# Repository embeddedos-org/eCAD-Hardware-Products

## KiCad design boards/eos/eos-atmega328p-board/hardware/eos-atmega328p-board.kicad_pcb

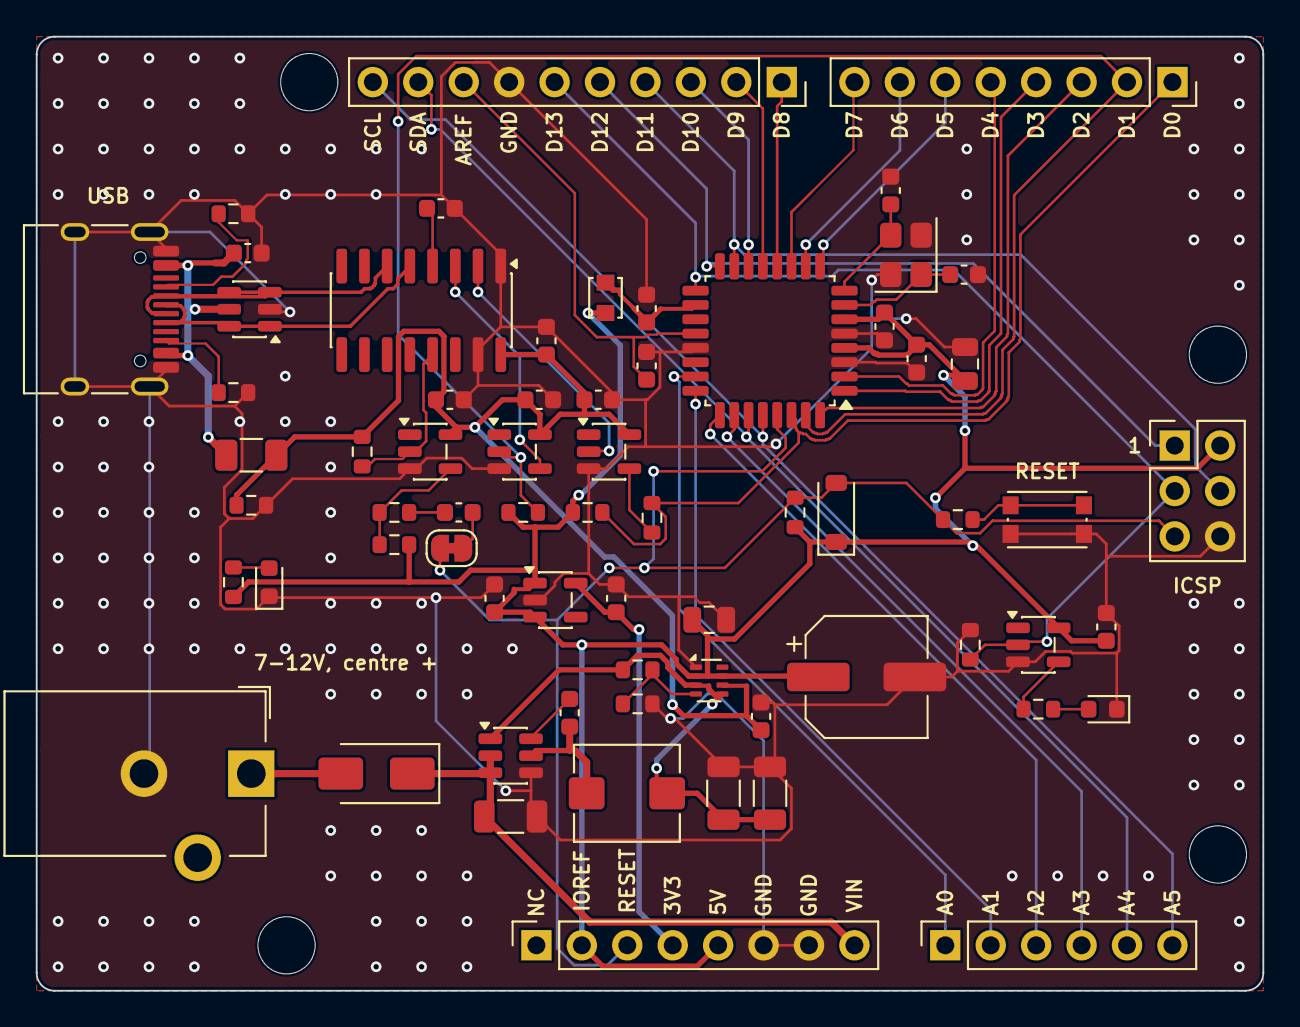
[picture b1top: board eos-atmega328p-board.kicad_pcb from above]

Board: 2 copper layers, 68.6 x 53.3 mm, 71 parts (1 on the bottom side), 52 nets.

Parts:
C1: 10u; C_1206_3216Metric
C2, C9, C10, C11, C12, C13, C15, C16, C19, C21, C22, C23, C24: 100n; C_0603_1608Metric
C3, C4: 22u; C_1206_3216Metric
C5, C7, C8: 1u; C_0603_1608Metric
C6: 100u; CP_Elec_6.3x5.8
C14, C20: 10u; C_0805_2012Metric
C17, C18: 18p; C_0603_1608Metric
D1: B240A; D_SMA
D2: PWR; LED_0603_1608Metric
D3: 1N4148W; D_SOD-123
D4: L; LED_0603_1608Metric
F1: 500mA; Fuse_1206_3216Metric
H1, H2, H3, H4: M3; MountingHole_3.2mm_M3_ISO14580
J1: USB-C; USB_C_Receptacle_HRO_TYPE-C-31-M-12
J2: 7-12V; BarrelJack_CUI_PJ-102AH_Horizontal
J3: D0-D7; PinSocket_1x08_P2.54mm_Vertical
J4: D8-SCL; PinSocket_1x10_P2.54mm_Vertical
J5: POWER; PinSocket_1x08_P2.54mm_Vertical
J6: A0-A5; PinSocket_1x06_P2.54mm_Vertical
J7: ICSP; PinHeader_2x03_P2.54mm_Vertical
JP1: AUTO-RST; SolderJumper-2_P1.3mm_Bridged_RoundedPad1.0x1.5mm
L1: 4.7u; L_Bourns_SRP5030T
L2: 10u; L_Murata_LQH2MCNxxxx02_2.0x1.6mm
R1, R2: 5.1k; R_0603_1608Metric
R3: 33k; R_0603_1608Metric
R4, R8, R13, R14, R15: 10k; R_0603_1608Metric
R5, R11: 1.5k; R_0603_1608Metric
R6: 1k; R_0603_1608Metric
R7, R10, R16: 100k; R_0603_1608Metric
R9: 330; R_0603_1608Metric
R12: 220; R_0603_1608Metric
SW1: RESET; SW_Push_1P1T_NO_CK_KMR2
U1: USBLC6-2SC6; SOT-23-6
U2: AP63205; TSOT-23-6
U3: TPS2116; SOT-583-8
U4: AP2112K-3.3; SOT-23-5
U5: CH340C; SOIC-16_3.9x9.9mm_P1.27mm
U6: ATmega328P-AU; TQFP-32_7x7mm_P0.8mm
U7, U8, U9: SN74LVC1G17; SOT-23-5
U10: SN74LVC1G07; SOT-23-5
Y1: 16MHz; Crystal_SMD_3225-4Pin_3.2x2.5mm

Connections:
+3V3: C8.1, J5.4, U4.5
+5V: C6.1, C7.1, C12.1, C13.1, C14.1, C19.1, C20.1, D3.1, J5.2, J5.5, J7.2, L2.1, R5.1, R7.1, R8.1, R13.1, R15.2, U3.2, U3.7, U4.1, U4.3, U6.4, U6.6, U7.5
/5V_REG: C3.1, C4.1, L1.2, R3.1, U2.1, U3.3, U3.5
/A0: J6.1, U6.23
/A1: J6.2, U6.24
/A2: J6.3, U6.25
/A3: J6.4, U6.26
/A4_SDA: J4.9, J6.5, U6.27
/A5_SCL: J4.10, J6.6, U6.28
/AREF: C16.1, J4.8, U6.20
/AVCC: C15.1, L2.2, U6.18
/BUCK_BST: C2.2, U2.6
/BUCK_SW: C2.1, L1.1, U2.5
/CC1: J1.A5, R1.1
/CC2: J1.B5, R2.1
/CH_DTR: R16.1, U5.13, U10.2
/CH_RX: U5.3, U8.4
/CH_TX: U5.2, U9.2
/CH_V3: C10.1, U5.4
/D0: J3.1, R6.2, R13.2, U6.30
/D0_BUF: R6.1, U9.4
/D1: J3.2, R7.2, U6.31, U8.2
/D2: J3.3, U6.32
/D3: J3.4, U6.1
/D4: J3.5, U6.2
/D5: J3.6, U6.9
/D6: J3.7, U6.10
/D7: J3.8, U6.11
/D8: J4.1, U6.12
/D9: J4.2, U6.13
/D10: J4.3, U6.14
/D11: J4.4, J7.4, U6.15
/D12: J4.5, J7.1, U6.16
/D13: J4.6, J7.3, R10.1, U6.17, U7.2
/DTR_BUF: R12.1, R15.1, U10.4
/DTR_C: C11.1, R12.2
/DTR_JP: C11.2, JP1.1
/LED_L_A: D4.2, R11.2
/LED_L_DRV: R11.1, U7.4
/LED_PWR_A: D2.2, R5.2
/MUX_PR1: R3.2, R4.1, U3.4
/RESET: D3.2, J5.3, J7.5, JP1.2, R8.2, R9.1, U6.29
/RST_SW: R9.2, SW1.1
/USB_D+: J1.A6, J1.B6, U1.1, U1.6, U5.5
/USB_D-: J1.A7, J1.B7, U1.3, U1.4, U5.6
/VIN: C1.1, D1.1, J5.8, U2.2, U2.3
/VJACK: D1.2, J2.1
/VUSB: C5.1, C9.1, C22.1, C23.1, C24.1, F1.2, R14.1, R16.2, U3.6, U5.16, U8.5, U9.5, U10.5
/XTAL1: C17.1, U6.7, Y1.1
/XTAL2: C18.1, U6.8, Y1.3
GND: C1.2, C3.2, C4.2, C5.2, C6.2, C7.2, C8.2, C9.2, C10.2, C12.2, C13.2, C14.2, C15.2, C16.2, C17.2, C18.2, C19.2, C20.2, C21.2, C22.2, C23.2, C24.2, D2.1, D4.1, J1.A1, J1.A12, J1.B1, J1.B12, J1.SH, J2.2, J4.7, J5.6, J5.7, J7.6, R1.2, R2.2, R4.2, R10.2, R14.2, SW1.2, U1.2, U2.4, U3.1, U4.2, U5.1, U5.15, U6.3, U6.5, U6.21, U7.3, U8.3, U9.3, U10.3, Y1.2, Y1.4
VBUS: C21.1, F1.1, J1.A4, J1.A9, J1.B4, J1.B9, U1.5

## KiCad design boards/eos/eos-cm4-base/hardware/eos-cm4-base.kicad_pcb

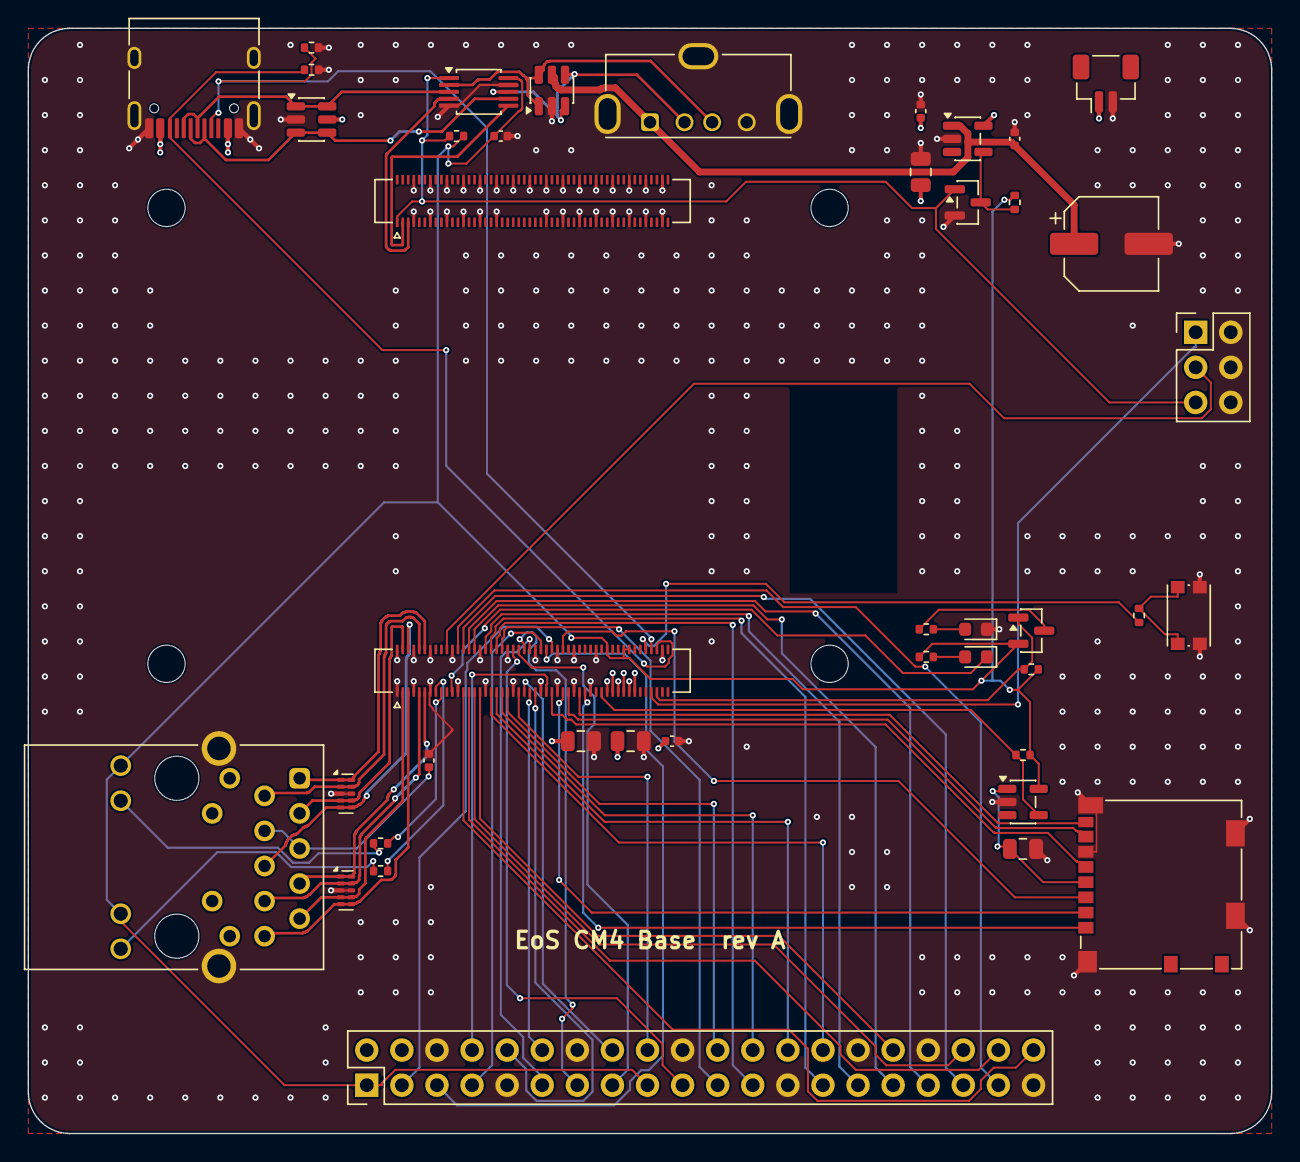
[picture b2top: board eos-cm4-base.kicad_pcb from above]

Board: 4 copper layers, 90.0 x 80.0 mm, 46 parts (0 on the bottom side), 72 nets.

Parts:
C1, C2, C5, C8: 10u; C_0805_2012Metric
C3, C4, C7, C9, C10: 100n; C_0402_1005Metric
C6: 150u; CP_Elec_6.3x5.8
D1: PWR; LED_0603_1608Metric
D2: ACT; LED_0603_1608Metric
H1, H2, H3, H4: M2.5; MountingHole_2.7mm_M2.5
J1: CM4 1-100; Hirose_DF40C-100DS-0.4V_2x50_P0.4mm
J2: CM4 101-200; Hirose_DF40C-100DS-0.4V_2x50_P0.4mm
J3: USB-C; USB_C_Receptacle_HRO_TYPE-C-31-M-12
J4: USB-A; USB_A_Molex_105057_Vertical
J5: TRJG0926HENL; TRXCOM_TRJG0926HENL
J6: microSD; microSD_HC_Molex_104031-0811
J7: GPIO; PinHeader_2x20_P2.54mm_Vertical
J8: FAN; JST_SH_BM02B-SRSS-TB_1x02-1MP_P1.00mm_Vertical
J9: BOOT; PinHeader_2x03_P2.54mm_Vertical
Q1: BSS84; SOT-23
Q2: 2N7002; SOT-23
R1, R2: 470; R_0402_1005Metric
R3, R10, R11: 10k; R_0402_1005Metric
R4, R5: 1k; R_0402_1005Metric
R6, R7: 5.1k; R_0402_1005Metric
R8: 220; R_0402_1005Metric
R9: 100k; R_0402_1005Metric
SW1: RESET; SW_Push_1P1T_NO_CK_KMR2
U1, U3: USBLC6-2SC6; SOT-23-6
U2: TPS2051C; SOT-23-5
U4, U5: TPD4EUSB30; USON-10_2.5x1.0mm_P0.5mm
U6: RT9742GGJ5; TSOT-23-5
U7: TS3USB30E; TSSOP-10_3x3mm_P0.5mm

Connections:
+3V3: C9.1, J1.78, J1.84, J1.86, J5.15, J5.17, J7.1, J7.17, Q1.2, R3.2, R5.1, R9.2, R10.2, R11.2, U6.5, U7.10
+5V: C1.1, C2.1, C3.1, C4.1, C5.1, J1.77, J1.79, J1.81, J1.83, J1.85, J1.87, J3.A4, J3.A9, J3.B4, J3.B9, J7.2, J7.4, J8.1, U1.5, U2.5
/CC1: J1.94, J3.A5, R6.1
/CC2: J1.96, J3.B5, R7.1
/EEPROM_NWP: J1.20, J9.3
/ETH_A_N: J1.10, J5.2, U4.2, U4.9
/ETH_A_P: J1.12, J5.1, U4.1, U4.10
/ETH_B_N: J1.6, J5.6, U4.5, U4.6
/ETH_B_P: J1.4, J5.3, U4.4, U4.7
/ETH_CT: C7.1, J5.4, J5.5
/ETH_C_N: J1.9, J5.8, U5.2, U5.9
/ETH_C_P: J1.11, J5.7, U5.1, U5.10
/ETH_D_N: J1.5, J5.10, U5.5, U5.6
/ETH_D_P: J1.3, J5.9, U5.4, U5.7
/ETH_LEDG_K: J5.18, R2.1
/ETH_LEDY_K: J5.16, R1.1
/ETH_NLED_ACT: J1.15, R2.2
/ETH_NLED_SPD: J1.17, R1.2
/GPIO2: J1.58, J7.3
/GPIO3: J1.56, J7.5
/GPIO4: J1.54, J7.7
/GPIO5: J1.34, J7.29
/GPIO6: J1.30, J7.31
/GPIO7: J1.37, J7.26
/GPIO8: J1.39, J7.24
/GPIO9: J1.40, J7.21
/GPIO10: J1.44, J7.19
/GPIO11: J1.38, J7.23
/GPIO12: J1.31, J7.32
/GPIO13: J1.28, J7.33
/GPIO14: J1.55, J7.8
/GPIO15: J1.51, J7.10
/GPIO16: J1.29, J7.36
/GPIO17: J1.50, J7.11
/GPIO18: J1.49, J7.12
/GPIO19: J1.26, J7.35
/GPIO20: J1.27, J7.38
/GPIO21: J1.25, J7.40
/GPIO22: J1.46, J7.15
/GPIO23: J1.47, J7.16
/GPIO24: J1.45, J7.18
/GPIO25: J1.41, J7.22
/GPIO26: J1.24, J7.37
/GPIO27: J1.48, J7.13
/ID_SC: J1.35, J7.28
/ID_SD: J1.36, J7.27
/LED_ACT_A: D2.2, R5.2
/LED_NACT: D2.1, J1.21
/LED_PWR_A: D1.2, R4.2
/LED_PWR_D: Q1.3, R4.1
/NRPIBOOT: J1.93, J9.1
/OTG_ID: J2.1, J9.5, Q2.1, R10.1, U7.1
/PI_LED_NPWR: J1.95, Q1.1, R9.1
/RUN_PG: J1.92, R8.1
/RUN_RST: R8.2, SW1.1
/SD_CLK: J1.57, J6.5
/SD_CMD: J1.62, J6.3
/SD_DAT0: J1.63, J6.7
/SD_DAT1: J1.67, J6.8
/SD_DAT2: J1.69, J6.1
/SD_DAT3: J1.61, J6.2
/SD_PWR_ON: J1.75, R3.1, U6.4
/SD_VDD: C8.1, J6.4, U6.1
/USBC_DM: J3.A7, J3.B7, U1.3, U1.4, U7.7
/USBC_DP: J3.A6, J3.B6, U1.1, U1.6, U7.3
/USBH_DM: J4.2, U3.3, U3.4, U7.8
/USBH_DP: J4.3, U3.1, U3.6, U7.2
/USBH_EN: Q2.3, R11.1, U2.4
/USBH_VBUS: C6.1, C10.1, J4.1, U2.1, U3.5
/USB_N: J2.3, U7.6
/USB_P: J2.5, U7.4
GND: C1.2, C2.2, C3.2, C4.2, C5.2, C6.2, C7.2, C8.2, C9.2, C10.2, D1.1, J1.1, J1.2, J1.7, J1.8, J1.13, J1.14, J1.22, J1.23, J1.32, J1.33, J1.42, J1.43, J1.52, J1.53, J1.59, J1.60, J1.65, J1.66, J1.71, J1.74, J1.98, J2.7, J2.8, J2.13, J2.14, J2.19, J2.20, J2.25, J2.26, J2.31, J2.32, J2.37, J2.38, J2.44, J2.50, J2.55, J2.56, J2.61, J2.62, J2.67, J2.68, J2.73, J2.74, J2.79, J2.80, J2.85, J2.86, J2.91, J2.92, J2.97, J2.98, J3.A1, J3.A12, J3.B1, J3.B12, J3.SH, J4.4, J4.SH, J5.19, J5.20, J6.6, J6.SH, J7.6, J7.9, J7.14, J7.20, J7.25, J7.30, J7.34, J7.39, J8.2, J9.2, J9.4, J9.6, Q2.2, R6.2, R7.2, SW1.2, U1.2, U2.2, U3.2, U4.3, U4.8, U5.3, U5.8, U6.2, U7.5, U7.9

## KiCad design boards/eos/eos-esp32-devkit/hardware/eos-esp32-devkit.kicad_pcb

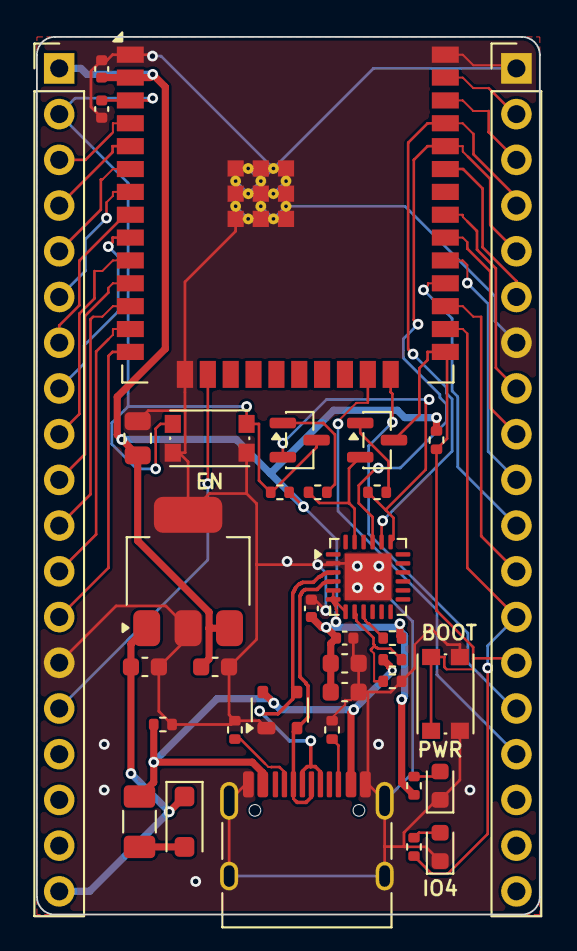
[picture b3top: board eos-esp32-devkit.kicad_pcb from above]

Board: 2 copper layers, 27.9 x 48.8 mm, 36 parts (0 on the bottom side), 44 nets.

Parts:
C1, C2, C6, C8: 4.7u; C_0603_1608Metric
C3, C7, C9: 100n; C_0402_1005Metric
C4: 22u; C_0805_2012Metric
C5: 1u; C_0402_1005Metric
D1: PMEG6010CEH; D_SOD-123F
D2: PWR; LED_0603_1608Metric
D3: IO4; LED_0603_1608Metric
F1: 500mA; Fuse_1206_3216Metric
J1: USB-C; USB_C_Receptacle_HRO_TYPE-C-31-M-12
J2: J2; PinHeader_1x19_P2.54mm_Vertical
J3: J3; PinHeader_1x19_P2.54mm_Vertical
Q1, Q2: MMBT3904; SOT-23
R1, R2, R12: 5.1k; R_0402_1005Metric
R3: 750; R_0402_1005Metric
R4, R5, R10, R11: 10k; R_0402_1005Metric
R6: 680; R_0402_1005Metric
R7: 1k; R_0402_1005Metric
R8: 22.1k; R_0402_1005Metric
R9: 47.5k; R_0402_1005Metric
SW1: EN; SW_Push_1P1T_NO_CK_KMR2
SW2: BOOT; SW_Push_1P1T_NO_CK_KMR2
U1: ESP32-WROOM-32E-N4; ESP32-WROOM-32E
U2: SP0503BAHTG; SOT-143
U3: AP7361C-33; SOT-223-3_TabPin2
U4: CP2102N-A02-GQFN24; QFN-24-1EP_4x4mm_P0.5mm_EP2.6x2.6mm

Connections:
+3V3: C2.1, C3.1, C4.1, C6.1, C7.1, C8.1, C9.1, J2.1, R3.1, R4.2, R5.2, R7.2, U1.2, U3.3, U4.5, U4.6, U4.7
+5V: C1.1, D1.1, J2.19, U3.1
/CC1: J1.A5, R1.1
/CC2: J1.B5, R2.1
/CP_RST: R7.1, U4.9
/DTR: Q2.2, R10.1, U4.23
/EN: C5.2, J2.2, Q1.3, R4.1, SW1.1, U1.3
/IO0: J3.14, Q2.3, R5.1, SW2.1, U1.25
/IO2: J3.15, U1.24
/IO4: J3.13, R6.1, U1.26
/IO5: J3.10, U1.29
/IO12: J2.13, U1.14
/IO13: J2.15, U1.16
/IO14: J2.12, U1.13
/IO15: J3.16, U1.23
/IO16: J3.12, U1.27
/IO17: J3.11, U1.28
/IO18: J3.9, U1.30
/IO19: J3.8, U1.31
/IO21: J3.6, U1.33
/IO22: J3.3, U1.36
/IO23: J3.2, U1.37
/IO25: J2.9, U1.10
/IO26: J2.10, U1.11
/IO27: J2.11, U1.12
/IO32: J2.7, U1.8
/IO33: J2.8, U1.9
/IO34: J2.5, U1.6
/IO35: J2.6, U1.7
/IO36: J2.3, U1.4
/IO39: J2.4, U1.5
/LED_PWR_A: D2.2, R3.2
/LED_USR_A: D3.2, R6.2
/QB1: Q1.1, R10.2
/QB2: Q2.1, R11.2
/RTS: Q1.2, R11.1, U4.19
/U0RXD: J3.5, U1.34, U4.21
/U0TXD: J3.4, U1.35, U4.20
/USB_D+: J1.A6, J1.B6, U2.3, U4.3
/USB_D-: J1.A7, J1.B7, U2.2, U4.4
/VBUS_F: D1.2, F1.2
/VBUS_SENSE: R8.2, R9.1, U4.8
GND: C1.2, C2.2, C3.2, C4.2, C5.1, C6.2, C7.2, C8.2, C9.2, D2.1, D3.1, J1.A1, J1.A12, J1.B1, J1.B12, J1.SH, J2.14, J3.1, J3.7, R1.2, R2.2, R9.2, R12.2, SW1.2, SW2.2, U1.1, U1.15, U1.38, U1.39, U2.1, U3.2, U4.2, U4.25
VBUS: F1.1, J1.A4, J1.A9, J1.B4, J1.B9, R8.1, R12.1, U2.4

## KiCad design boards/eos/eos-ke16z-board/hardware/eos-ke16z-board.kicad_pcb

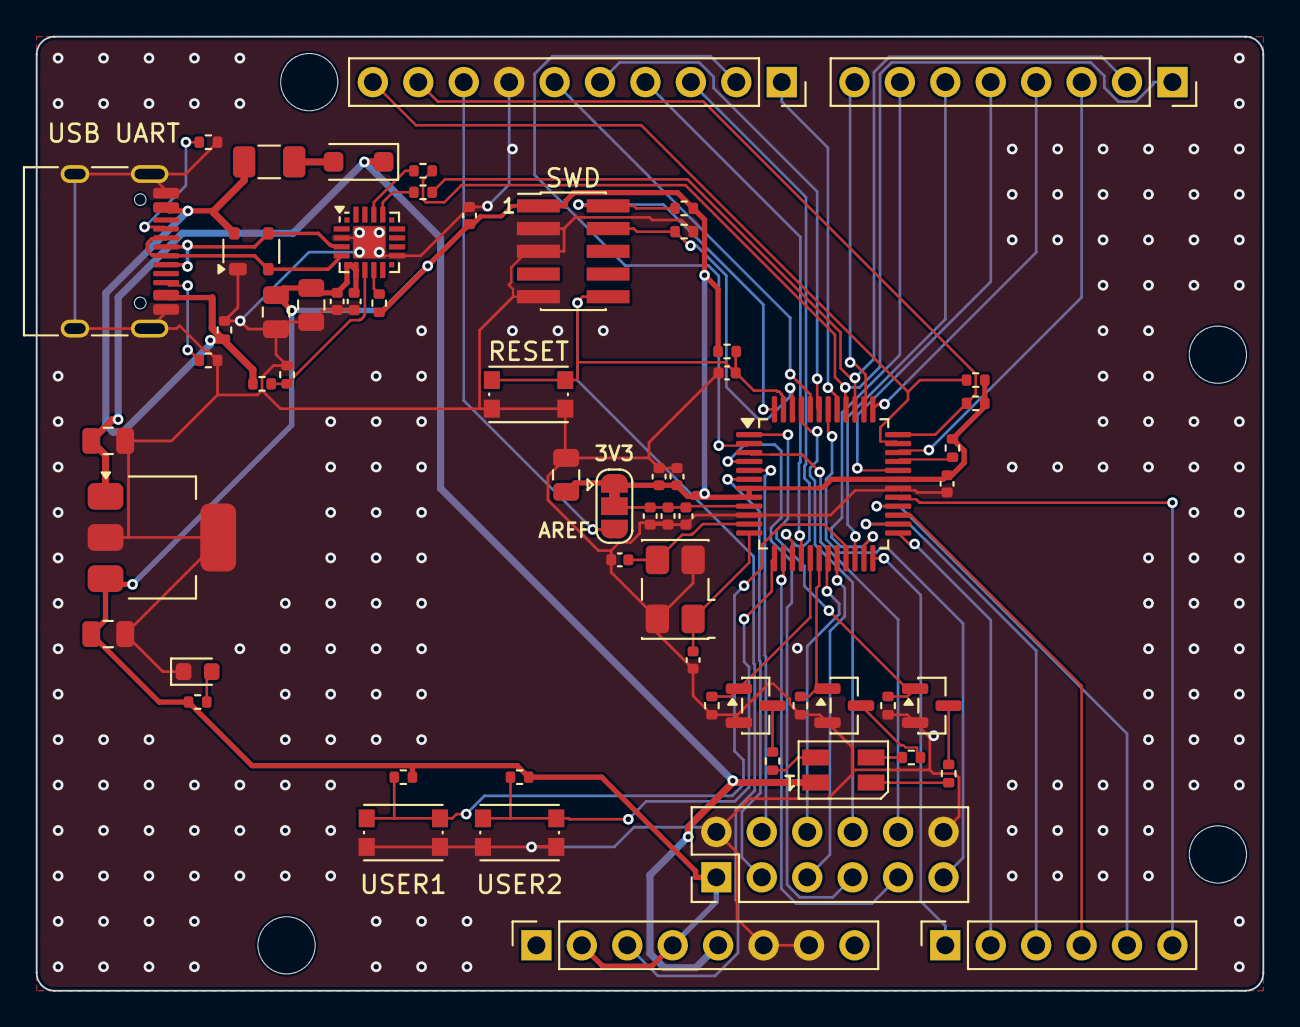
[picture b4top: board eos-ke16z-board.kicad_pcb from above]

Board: 2 copper layers, 68.6 x 53.3 mm, 67 parts (1 on the bottom side), 64 nets.

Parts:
C1, C2, C3, C5: 4.7u; C_0805_2012Metric
C4, C6, C7, C8, C9, C11, C16, C17: 100n; C_0402_1005Metric
C10: 10u; C_0805_2012Metric
C12: 10n; C_0402_1005Metric
C13: 1n; C_0402_1005Metric
C14, C15: 11p; C_0402_1005Metric
D1: PMEG6010CEH; D_SOD-123F
D2: PWR; LED_0603_1608Metric
D3: RGB; LED_RGB_Wuerth-PLCC4_3.2x2.8mm_150141M173100
F1: 500mA; Fuse_1206_3216Metric
H1, H2, H3, H4: M3; MountingHole_3.2mm_M3_ISO14580
J1: USB-C; USB_C_Receptacle_HRO_TYPE-C-31-M-12
J2: SWD; PinHeader_2x05_P1.27mm_Vertical_SMD
J3: D8-SCL; PinSocket_1x10_P2.54mm_Vertical
J4: D0-D7; PinSocket_1x08_P2.54mm_Vertical
J5: POWER; PinSocket_1x08_P2.54mm_Vertical
J6: A0-A5; PinSocket_1x06_P2.54mm_Vertical
J7: EXT; PinHeader_2x06_P2.54mm_Vertical
JP1: VREFH; SolderJumper-3_P1.3mm_Bridged12_RoundedPad1.0x1.5mm
Q1, Q2, Q3: AO3400A; SOT-23
R1, R2, R5: 5.1k; R_0402_1005Metric
R3: 680; R_0402_1005Metric
R4, R8, R9: 1k; R_0402_1005Metric
R6: 22.1k; R_0402_1005Metric
R7: 47.5k; R_0402_1005Metric
R10, R11, R12, R13, R14, R15: 10k; R_0402_1005Metric
R16: 560; R_0402_1005Metric
R17, R18: 300; R_0402_1005Metric
R19, R20, R21: 100k; R_0402_1005Metric
R22, R23: 4.7k; R_0402_1005Metric
SW1: RESET; SW_Push_1P1T_NO_CK_KMR2
SW2: USER1; SW_Push_1P1T_NO_CK_KMR2
SW3: USER2; SW_Push_1P1T_NO_CK_KMR2
U1: SP0503BAHTG; SOT-143
U2: CP2102N-A02-GQFN20; SiliconLabs_QFN-20-1EP_3x3mm_P0.5mm_EP1.8x1.8mm
U3: AP7361C-33; SOT-223-3_TabPin2
U4: MKE16Z64VLF4; LQFP-48_7x7mm_P0.5mm
Y1: 8MHz; Crystal_SMD_5032-4Pin_5.0x3.2mm

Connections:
+3V3: C2.1, C3.1, C4.1, C5.1, C6.1, C7.1, C8.1, C9.1, C10.1, C17.1, J2.1, J5.2, J5.4, J7.1, JP1.1, R3.1, R4.2, R10.2, R11.2, R12.2, R14.2, R15.2, R22.2, R23.2, U2.6, U2.7, U3.3, U4.7, U4.8, U4.31
+5V: C1.1, D1.1, D3.1, J5.5, U3.1
/A0: J6.1, U4.24
/A1: J6.2, U4.25
/A2: J6.3, U4.26
/A3: J6.4, U4.27
/A4: J6.5, U4.28
/A5: J6.6, U4.29
/AREF: J3.8, JP1.3
/BR_RST: R4.1, U2.9
/BR_RXD: R9.2, U2.17
/BR_TXD: R8.1, U2.18
/BR_VBUS: R6.2, R7.1, U2.8
/BTN1: R14.1, SW2.1, U4.21
/BTN2: R15.1, SW3.1, U4.13
/CC1: J1.A5, R1.1
/CC2: J1.B5, R2.1
/D0: J4.1, R8.2, U4.40
/D1: J4.2, R9.1, U4.39
/D2: J4.3, U4.34
/D3: J4.4, U4.37
/D4: J4.5, U4.32
/D5: J4.6, U4.22
/D6: J4.7, U4.23
/D7: J4.8, U4.38
/D8: J3.1, U4.41
/D9: J3.2, U4.2
/D10: J3.3, U4.15
/D11: J3.4, U4.16
/D12: J3.5, U4.43
/D13: J3.6, U4.44
/EXTAL: C14.1, U4.11, Y1.3
/EXT_PTC5: J7.8, U4.45
/EXT_PTD6: J7.5, U4.20
/EXT_PTD7: J7.6, U4.19
/EXT_PTE2: J7.11, U4.42
/EXT_PTE4: J7.3, U4.6
/EXT_PTE5: J7.4, U4.5
/EXT_PTE8: J7.9, U4.14
/EXT_PTE10: J7.7, U4.4
/EXT_PTE11: J7.10, U4.3
/LED_B: Q3.1, R21.1, U4.17
/LED_G: Q2.1, R20.1, U4.18
/LED_PWR_A: D2.2, R3.2
/LED_R: Q1.1, R19.1, U4.1
/NMI: R11.1, U4.33
/RESET: C16.1, J2.10, J5.3, R10.1, SW1.1, U4.47
/RGB_BD: Q3.3, R18.2
/RGB_BK: D3.2, R18.1
/RGB_GD: Q2.3, R17.2
/RGB_GK: D3.4, R17.1
/RGB_RD: Q1.3, R16.2
/RGB_RK: D3.3, R16.1
/SCL: J3.10, R23.1, U4.35
/SDA: J3.9, R22.1, U4.36
/SWCLK: J2.4, R13.1, U4.46
/SWDIO: J2.2, R12.1, U4.48
/USB_DM: J1.A7, J1.B7, U1.2, U2.5
/USB_DP: J1.A6, J1.B6, U1.3, U2.4
/VBUS: F1.1, J1.A4, J1.A9, J1.B4, J1.B9, R5.1, R6.1, U1.4
/VBUS_F: D1.2, F1.2
/VREFH: C11.1, C12.1, C13.1, JP1.2, U4.9
/XTAL: C15.1, U4.12, Y1.1
GND: C1.2, C2.2, C3.2, C4.2, C5.2, C6.2, C7.2, C8.2, C9.2, C10.2, C11.2, C12.2, C13.2, C14.2, C15.2, C16.2, C17.2, D2.1, J1.A1, J1.A12, J1.B1, J1.B12, J1.SH, J2.3, J2.5, J2.9, J3.7, J5.6, J5.7, J7.2, J7.12, Q1.2, Q2.2, Q3.2, R1.2, R2.2, R5.2, R7.2, R13.2, R19.2, R20.2, R21.2, SW1.2, SW2.2, SW3.2, U1.1, U2.3, U2.12, U2.21, U3.2, U4.10, U4.30, Y1.2, Y1.4

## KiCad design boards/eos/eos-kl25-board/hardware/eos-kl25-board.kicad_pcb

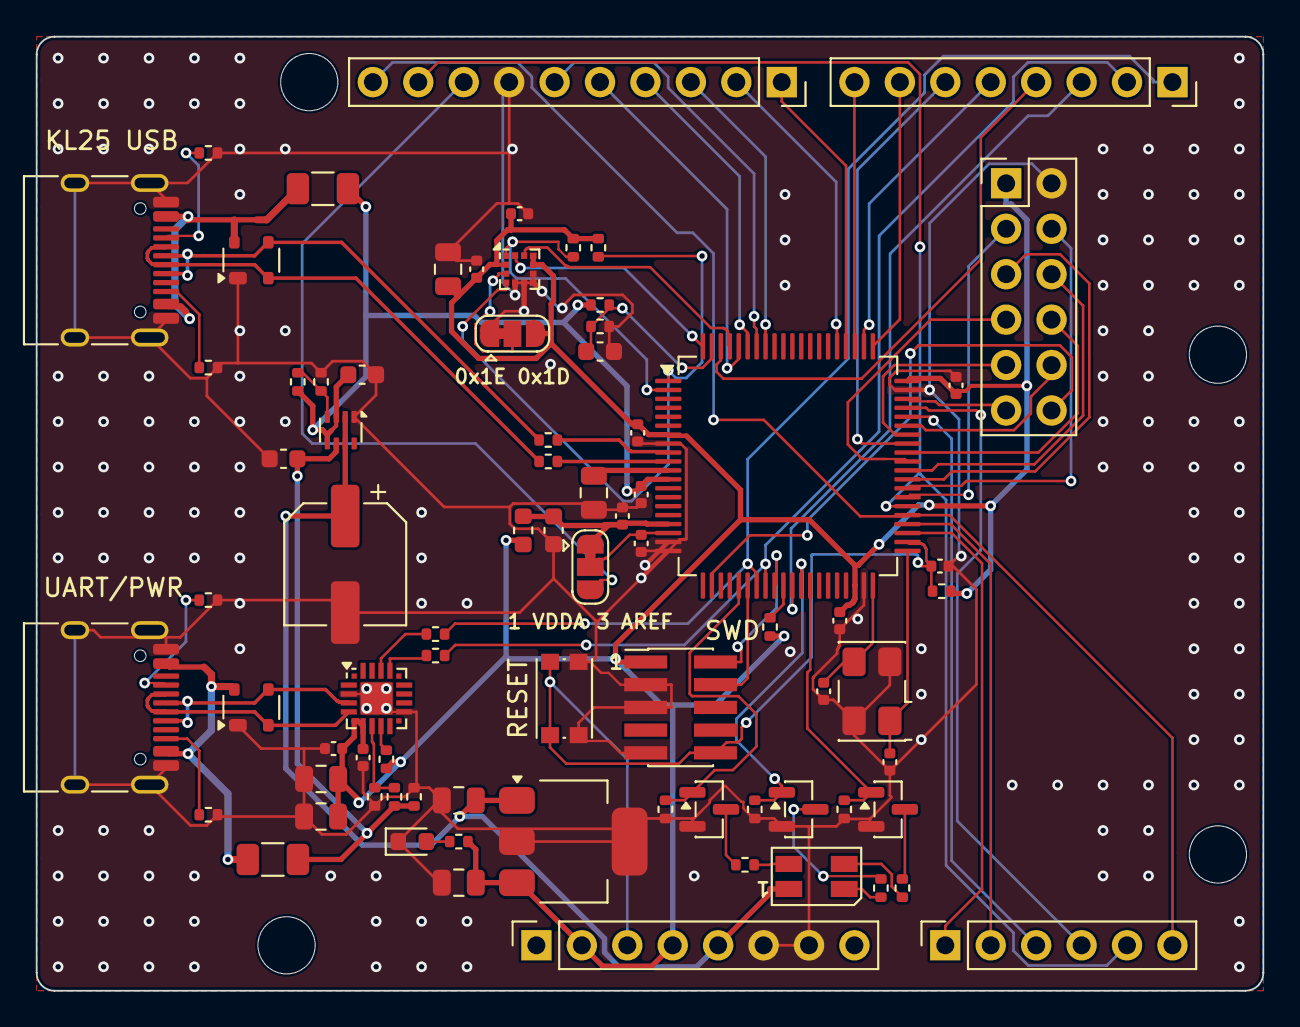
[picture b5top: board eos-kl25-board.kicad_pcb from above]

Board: 2 copper layers, 68.6 x 53.3 mm, 82 parts (1 on the bottom side), 78 nets.

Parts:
C1, C2, C12, C24: 1u; C_0603_1608Metric
C3: 100u; CP_Elec_6.3x5.8
C4, C5, C7, C17, C19: 4.7u; C_0805_2012Metric
C6, C8, C9, C10, C11, C13, C16, C18, C20, C21, C22: 100n; C_0402_1005Metric
C14, C15: 11p; C_0402_1005Metric
C23: 10u; C_0805_2012Metric
D1: PWR; LED_0603_1608Metric
D2: RGB; LED_RGB_Wuerth-PLCC4_3.2x2.8mm_150141M173100
F1, F2: 500mA; Fuse_1206_3216Metric
FB1: 220R; L_0603_1608Metric
H1, H2, H3, H4: M3; MountingHole_3.2mm_M3_ISO14580
J1, J2: USB-C; USB_C_Receptacle_HRO_TYPE-C-31-M-12
J3: D8-SCL; PinSocket_1x10_P2.54mm_Vertical
J4: D0-D7; PinSocket_1x08_P2.54mm_Vertical
J5: POWER; PinSocket_1x08_P2.54mm_Vertical
J6: A0-A5; PinSocket_1x06_P2.54mm_Vertical
J7: SWD; PinHeader_2x05_P1.27mm_Vertical_SMD
J8: EXT; PinHeader_2x06_P2.54mm_Vertical
JP1: VREFH; SolderJumper-3_P1.3mm_Bridged12_RoundedPad1.0x1.5mm
JP2: 0x1E; SolderJumper-3_P1.3mm_Bridged12_RoundedPad1.0x1.5mm
Q1, Q2, Q3: AO3400A; SOT-23
R1, R2, R3, R4: 5.1k; R_0402_1005Metric
R5, R6: 33; R_0402_1005Metric
R7: 15k; R_0402_1005Metric
R8: 22k; R_0402_1005Metric
R9: 27k; R_0402_1005Metric
R10, R12, R13, R27: 10k; R_0402_1005Metric
R11: 680; R_0402_1005Metric
R14, R17, R18: 1k; R_0402_1005Metric
R15: 22.1k; R_0402_1005Metric
R16: 47.5k; R_0402_1005Metric
R19, R20: 4.7k; R_0402_1005Metric
R21: 620; R_0402_1005Metric
R22, R23: 360; R_0402_1005Metric
R24, R25, R26: 100k; R_0402_1005Metric
SW1: RESET; SW_Push_1P1T_NO_CK_KMR2
U1, U2: SP0503BAHTG; SOT-143
U3: TPS2116; SOT-583-8
U4: AP7361C-33; SOT-223-3_TabPin2
U5: MKL25Z128VLK4; LQFP-80_12x12mm_P0.5mm
U6: CP2102N-A02-GQFN20; SiliconLabs_QFN-20-1EP_3x3mm_P0.5mm_EP1.8x1.8mm
U7: LIS2HH12; LGA-12_2x2mm_P0.5mm
Y1: 8MHz; Crystal_SMD_5032-4Pin_5.0x3.2mm

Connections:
+3V3: C5.1, C8.1, C9.1, C10.1, C17.1, C18.1, C19.1, C20.1, C21.1, C22.1, C23.1, FB1.1, J5.2, J5.4, J7.1, J8.1, JP2.3, R11.1, R12.2, R13.2, R14.2, R19.2, R20.2, U4.3, U5.7, U5.38, U5.60, U6.6, U6.7, U7.2, U7.9, U7.10
+5V: C3.1, C4.1, D2.1, J5.5, U3.2, U3.7, U4.1
/A0: J6.1, U5.43
/A1: J6.2, U5.44
/A2: J6.3, U5.56
/A3: J6.4, U5.57
/A4_SDA: J3.9, J6.5, U5.46
/A5_SCL: J3.10, J6.6, U5.45
/ACC_INT1: U5.80, U7.12
/ACC_INT2: U5.77, U7.11
/ACC_SA0: JP2.2, U7.3
/ACC_SCL: R19.1, U5.2, U7.1
/ACC_SDA: R20.1, U5.1, U7.4
/AREF: J3.8, JP1.3
/BR_RST: R14.1, U6.9
/BR_RXD: R18.2, U6.17
/BR_TXD: R17.1, U6.18
/BR_VBUS: R15.2, R16.1, U6.8
/CC1A: J1.A5, R1.1
/CC1B: J2.A5, R3.1
/CC2A: J1.B5, R2.1
/CC2B: J2.B5, R4.1
/D0: J4.1, R17.2, U5.27
/D1: J4.2, R18.1, U5.28
/D2: J4.3, U5.31
/D3: J4.4, U5.78
/D4: J4.5, U5.62
/D5: J4.6, U5.53
/D6: J4.7, U5.61
/D7: J4.8, U5.63
/D8: J3.1, U5.64
/D9: J3.2, U5.65
/D10: J3.3, U5.73
/D11: J3.4, U5.75
/D12: J3.5, U5.76
/D13: J3.6, U5.74
/EXT_PTB8: J8.3, U5.47
/EXT_PTB9: J8.4, U5.48
/EXT_PTB10: J8.5, U5.49
/EXT_PTB11: J8.6, U5.50
/EXT_PTB16: J8.7, U5.51
/EXT_PTB17: J8.8, U5.52
/EXT_PTB19: J8.9, U5.54
/EXT_PTC0: J8.10, U5.55
/EXT_PTC3: J8.11, U5.58
/EXT_PTE30: J8.12, U5.22
/KL_DM: R6.2, U5.10
/KL_DP: R5.2, U5.9
/LED_B: Q3.1, R26.1, U5.25
/LED_G: Q2.1, R25.1, U5.33
/LED_PWR_A: D1.2, R11.2
/LED_R: Q1.1, R24.1, U5.32
/MUX_PR1: R9.2, R10.1, U3.4
/NMI: R13.1, U5.30
/RESET: C16.1, J5.3, J7.10, R12.1, SW1.1, U5.42
/RGB_BD: Q3.3, R23.2
/RGB_BK: D2.2, R23.1
/RGB_GD: Q2.3, R22.2
/RGB_GK: D2.4, R22.1
/RGB_RD: Q1.3, R21.2
/RGB_RK: D2.3, R21.1
/SWCLK: J7.4, U5.26
/SWDIO: J7.2, U5.29
/USB1_DM: J1.A7, J1.B7, R6.1, U1.2
/USB1_DP: J1.A6, J1.B6, R5.1, U1.3
/USB2_DM: J2.A7, J2.B7, U2.2, U6.5
/USB2_DP: J2.A6, J2.B6, U2.3, U6.4
/VBUS1: F1.1, J1.A4, J1.A9, J1.B4, J1.B9, U1.4
/VBUS1_DET: C24.1, R7.2, R8.1, U5.79
/VBUS1_F: C1.1, C6.1, F1.2, R7.1, R9.1, U3.3, U3.5, U5.12
/VBUS2: F2.1, J2.A4, J2.A9, J2.B4, J2.B9, U2.4
/VBUS2_F: C2.1, F2.2, R15.1, R27.1, U3.6
/VDDA: C11.1, C12.1, FB1.2, JP1.1, U5.17
/VOUT33: C7.1, U5.11
/VREFH: C13.1, JP1.2, U5.18
/XTAL_IN: C14.1, U5.40, Y1.3
/XTAL_OUT: C15.1, U5.41, Y1.1
GND: C1.2, C2.2, C3.2, C4.2, C5.2, C6.2, C7.2, C8.2, C9.2, C10.2, C11.2, C12.2, C13.2, C14.2, C15.2, C16.2, C17.2, C18.2, C19.2, C20.2, C21.2, C22.2, C23.2, C24.2, D1.1, J1.A1, J1.A12, J1.B1, J1.B12, J1.SH, J2.A1, J2.A12, J2.B1, J2.B12, J2.SH, J3.7, J5.6, J5.7, J7.3, J7.5, J7.9, J8.2, JP2.1, Q1.2, Q2.2, Q3.2, R1.2, R2.2, R3.2, R4.2, R8.2, R10.2, R16.2, R24.2, R25.2, R26.2, R27.2, SW1.2, U1.1, U2.1, U3.1, U4.2, U5.8, U5.19, U5.20, U5.39, U5.59, U6.3, U6.12, U6.21, U7.5, U7.6, U7.7, U7.8, Y1.2, Y1.4

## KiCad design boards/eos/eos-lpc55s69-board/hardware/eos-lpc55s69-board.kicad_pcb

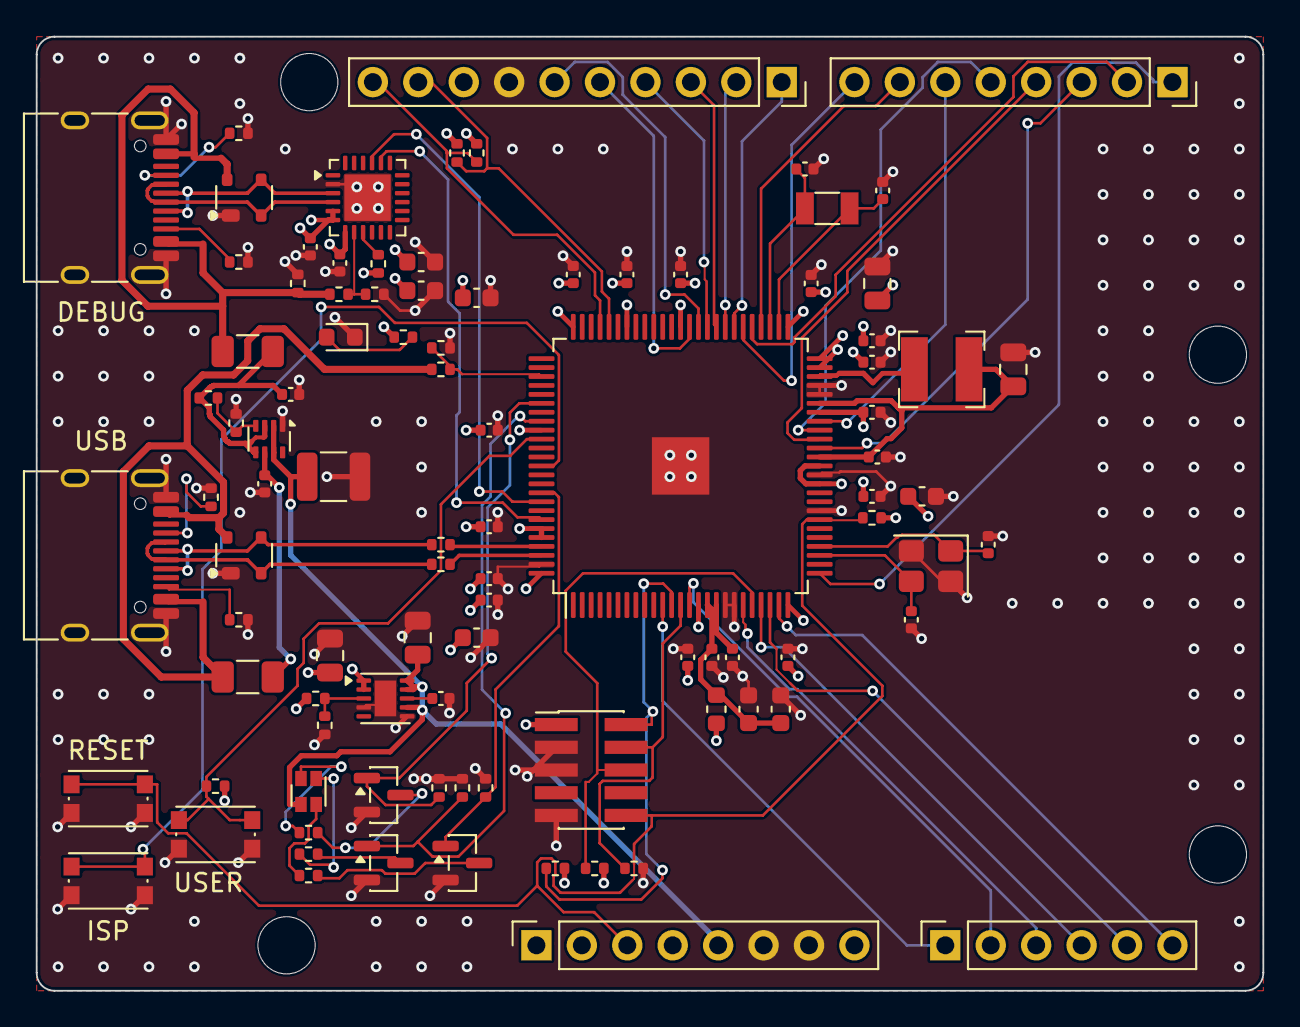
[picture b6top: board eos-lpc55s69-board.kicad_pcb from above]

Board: 4 copper layers, 68.6 x 53.3 mm, 99 parts (1 on the bottom side), 70 nets.

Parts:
C1, C2: 1u; C_0402_1005Metric
C3: 100u; C_1210_3225Metric
C4, C29, C33: 22u; C_0805_2012Metric
C5: 10u; C_0805_2012Metric
C6: 47n; C_0402_1005Metric
C7, C9: 4.7u; C_0603_1608Metric
C8, C10, C11, C12, C13, C14, C15, C16, C17, C18, C19, C21, C23, C25, C27, C30, C32, C34: 100n; C_0402_1005Metric
C20, C22, C24, C26, C28: 10u; C_0603_1608Metric
C31: 47p; C_0402_1005Metric
C35, C36: 11p; C_0402_1005Metric
C37, C38: 9p; C_0402_1005Metric
D1: PWR; LED_0603_1608Metric
D2: RGB; LED_LiteOn_LTST-C19HE1WT
F1, F2: 500mA; Fuse_1206_3216Metric
FB1: 220R; L_0603_1608Metric
H1, H2, H3, H4: M3; MountingHole_3.2mm_M3_ISO14580
J1, J2: USB-C; USB_C_Receptacle_HRO_TYPE-C-31-M-12
J3: Cortex Debug; PinHeader_2x05_P1.27mm_Vertical_SMD
J4: D8-SCL; PinSocket_1x10_P2.54mm_Vertical
J5: D0-D7; PinSocket_1x08_P2.54mm_Vertical
J6: POWER; PinSocket_1x08_P2.54mm_Vertical
J7: A0-A5; PinSocket_1x06_P2.54mm_Vertical
L1: 4.7u; L_Bourns-SRN4018
Q1, Q2, Q3: BSS138BK; SOT-23
R1, R2, R3, R4, R11: 5.1k; R_0402_1005Metric
R5, R6: 33; R_0402_1005Metric
R7: 4.7k; R_0402_1005Metric
R8: 6.8k; R_0402_1005Metric
R9: 22.1k; R_0402_1005Metric
R10: 47.5k; R_0402_1005Metric
R12: 27k; R_0402_1005Metric
R13, R18, R19, R20, R21, R22: 10k; R_0402_1005Metric
R14: 3.57k; R_0402_1005Metric
R15: 1.15k; R_0402_1005Metric
R16: 680; R_0402_1005Metric
R17: 1k; R_0402_1005Metric
R23, R24: 2.2k; R_0402_1005Metric
R25: 560; R_0402_1005Metric
R26, R27: 470; R_0402_1005Metric
R28, R29, R30: 100k; R_0402_1005Metric
SW1: RESET; SW_Push_1P1T_NO_CK_KMR2
SW2: ISP; SW_Push_1P1T_NO_CK_KMR2
SW3: USER; SW_Push_1P1T_NO_CK_KMR2
U1, U2: SP0503BAHTG; SOT-143
U3: TPS2116; SOT-583-8
U4: TPS7A91; Texas_S-PDSO-N10_EP1.2x2mm
U5: CP2102N-A02-GQFN24; QFN-24-1EP_4x4mm_P0.5mm_EP2.6x2.6mm
U6: LPC55S69JBD100; HLQFP-100-1EP_14x14mm_P0.5mm_EP3.21x3.21mm
Y1: 16MHz; Crystal_SMD_3225-4Pin_3.2x2.5mm
Y2: 32.768kHz; Crystal_SMD_3215-2Pin_3.2x1.5mm

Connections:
+3V3: C5.1, C7.1, C8.1, C9.1, C10.1, C11.1, C12.1, C13.1, C14.1, C15.1, C16.1, C17.1, C18.1, C19.1, C20.1, C21.1, C22.1, C23.1, C24.1, C29.1, C30.1, C31.1, C32.1, FB1.1, J3.1, J6.2, J6.4, R14.1, R16.1, R17.2, R18.2, R19.2, R20.2, R22.2, R23.2, R24.2, U4.1, U4.2, U5.5, U5.6, U5.7, U6.15, U6.25, U6.36, U6.38, U6.44, U6.49, U6.50, U6.51, U6.63, U6.69, U6.75, U6.84, U6.95, U6.96, U6.100
+5V: C3.1, C4.1, D2.4, J6.5, U3.2, U3.7, U4.7, U4.9, U4.10
/A0: J7.1, U6.11
/A1: J7.2, U6.14
/A2: J7.3, U6.20
/A3: J7.4, U6.22
/A4: J7.5, U6.23
/A5: J7.6, U6.24
/CP_RST: R17.1, U5.9
/CP_VBUS: R9.2, R10.1, U5.8
/D0: J5.1, U6.26
/D1: J5.2, U6.55
/D2: J5.3, U6.40
/D3: J5.4, U6.41
/D4: J5.5, U6.42
/D5: J5.6, U6.43
/D6: J5.7, U6.54
/D7: J5.8, U6.56
/D8: J4.1, U6.57
/D9: J4.2, U6.58
/D10: J4.3, U6.59
/D11: J4.4, U6.60
/D12: J4.5, U6.62
/D13: J4.6, U6.61
/DBG_CC1: J2.A5, R3.1
/DBG_CC2: J2.B5, R4.1
/DBG_C_DM: J2.A7, J2.B7, U2.2, U5.4
/DBG_C_DP: J2.A6, J2.B6, U2.3, U5.3
/DCDC_LX: L1.1, U6.48
/FC0_RXD: U5.21, U6.92
/FC0_TXD: U5.20, U6.94
/ISP_N: SW2.1, U6.88
/LDO_FB: R14.2, R15.1, U4.3
/LDO_NR: C6.1, U4.8
/LED_B: Q3.1, R30.1, U6.91
/LED_G: Q2.1, R29.1, U6.83
/LED_PWR_A: D1.2, R16.2
/LED_R: Q1.1, R28.1, U6.81
/MUX_PR1: R12.2, R13.1, U3.4
/RESETN: J3.10, J6.3, R20.1, SW1.1, U6.32
/RGB_BD: Q3.3, R27.2
/RGB_BK: D2.3, R27.1
/RGB_GD: Q2.3, R26.2
/RGB_GK: D2.2, R26.1
/RGB_RD: Q1.3, R25.2
/RGB_RK: D2.1, R25.1
/SCL: J4.10, R24.1, U6.72
/SDA: J4.9, R23.1, U6.71
/SWCLK: J3.4, R21.1, U6.13
/SWDIO: J3.2, R18.1, U6.12
/SWO: J3.6, R19.1, U6.21
/USB0_DM: R6.2, U6.98
/USB0_DP: R5.2, U6.97
/USB0_VBUS_S: R7.2, R8.1, U6.78
/USB_CC1: J1.A5, R1.1
/USB_CC2: J1.B5, R2.1
/USB_C_DM: J1.A7, J1.B7, R6.1, U1.2
/USB_C_DP: J1.A6, J1.B6, R5.1, U1.3
/USER_BTN: R22.1, SW3.1, U6.85
/VBUS_DBG: F2.1, J2.A4, J2.A9, J2.B4, J2.B9, R9.1, R11.1, U2.4
/VBUS_DBG_F: C1.1, F2.2, R12.1, U3.3, U3.5
/VBUS_USB: F1.1, J1.A4, J1.A9, J1.B4, J1.B9, R7.1, U1.4
/VBUS_USB_F: C2.1, F1.2, U3.6
/VDDA: C25.1, C26.1, C27.1, C28.1, FB1.2, U6.16, U6.17
/VDD_PMU: C33.1, C34.1, L1.2, U6.39, U6.45
/X32K_N: C38.1, U6.53, Y2.2
/X32K_P: C37.1, U6.52, Y2.1
/XTAL_N: C36.1, U6.28, Y1.3
/XTAL_P: C35.1, U6.29, Y1.1
GND: C1.2, C2.2, C3.2, C4.2, C5.2, C6.2, C7.2, C8.2, C9.2, C10.2, C11.2, C12.2, C13.2, C14.2, C15.2, C16.2, C17.2, C18.2, C19.2, C20.2, C21.2, C22.2, C23.2, C24.2, C25.2, C26.2, C27.2, C28.2, C29.2, C30.2, C31.2, C32.2, C33.2, C34.2, C35.2, C36.2, C37.2, C38.2, D1.1, J1.A1, J1.A12, J1.B1, J1.B12, J1.SH, J2.A1, J2.A12, J2.B1, J2.B12, J2.SH, J3.3, J3.5, J3.9, J4.7, J6.6, J6.7, Q1.2, Q2.2, Q3.2, R1.2, R2.2, R3.2, R4.2, R8.2, R10.2, R11.2, R13.2, R15.2, R21.2, R28.2, R29.2, R30.2, SW1.2, SW2.2, SW3.2, U1.1, U2.1, U3.1, U4.4, U4.6, U4.11, U5.2, U5.25, U6.18, U6.19, U6.33, U6.37, U6.46, U6.47, U6.99, U6.101, Y1.2, Y1.4

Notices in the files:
boards/eos/eos-atmega328p-board/hardware/eos-atmega328p-board.kicad_pcb:
(c) 2026 Kartikeydheer Srivastava
All rights reserved
